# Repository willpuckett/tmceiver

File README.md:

# TMCeiver

A drop in CAN transceiver for Robin Nano V3. 

TMCeiver utilizes a spare stepper slot on Robin Nano V3 to provide CAN connectivity. 

## Features

- CANFD capable (not yet supported in Klipper)
- Excellent reliability—no CAN retransmits in several months of testing
- Jumperable 120 Ω termination resistor
- Less cabling to crimp

## Installation

Start with power off.

1. Remove the stepper driver from the slot you want to use.
2. Make sure the steppers are jumpered to run at 5v. <br />
3. Use jumpers to jump the MISO and SCK pins to the TMCeiver. MISO and SCK are the first and third pins from the mcu side of the stepper slot.  If you're not sure, you can jumper the entire row (all four pins). <br /> or 
4. Insert TMCeiver into the slot, aligning the EN silkscreen with the EN slot on the board (for rev3, align the octule icon with EN). If you get it backwards, nothing will be damaged, but it won't work. <br />
5. Connect the CAN bus to the JST XH connector. 
6. Terminate the CAN bus by placing a jumper on the pins labeled `TERM`.
7. You can connect a second CAN device to the other JST XH connector, in which case you should remove the jumper from the `TERM` pins and terminate the bus at the last device.
8. Compile and flash your board (Use pins 'PD0/PD1' for the CAN bus) with the [Katapult](https://github.com/arksine/katapult) bootloader. You can build the Katapult Deployer and flash it via SD Card, or follow [these instructions](https://github.com/willpuckett/config/blob/main/reference/MKS/Robin_Nano_V3.1.md#flashing-katapult) to flash with OpenOCD.
9. Flash [Klipper](https://github.com/klipper3d/klipper). If you're connecting to the CAN bus with USB via the Robin Nano V3, you'll need to compile in CAN bus bridge mode. 

## Schematic

## Acquisition

Use the files in [production_files](jlcpcb/production_files/) directory to order the PCB from your favorite board house. If you're trying to lower costs, you can opt for assembly on the bottom side only, and hand solder the top side components.

There's also a couple available from my first run [here](https://octule.com).

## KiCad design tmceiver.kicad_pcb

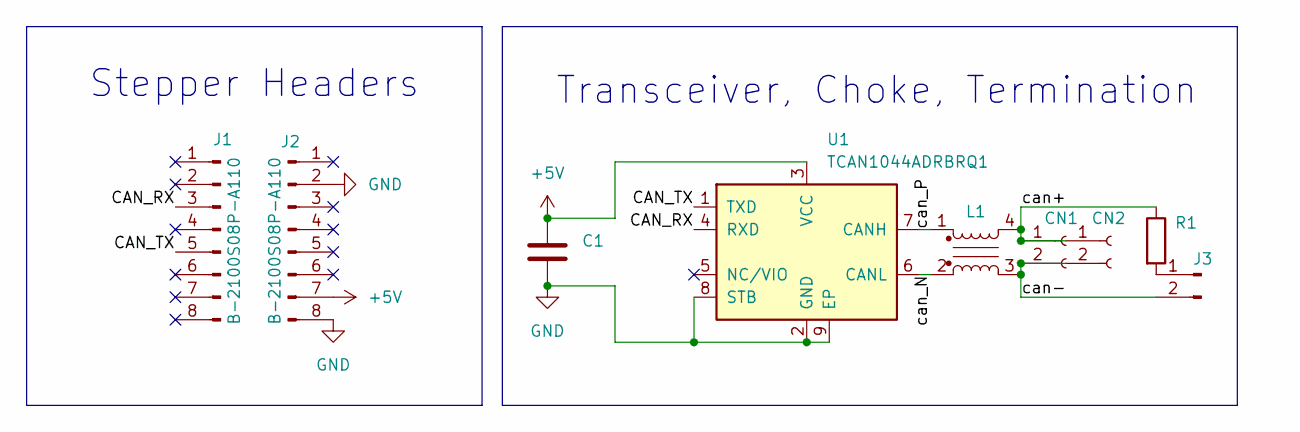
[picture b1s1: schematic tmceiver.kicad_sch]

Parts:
C1: CL10B104KB8NNNC; C_0603_1608Metric
CN1, CN2: B2B-XH-A (LF)(SN); JST_XH_B2B-XH-A_1x02_P2.50mm_Vertical
J1, J2: B-2100S08P-A110; PinHeader_1x08_P2.54mm_Vertical
J3: ZX-PZ2.0-1-2PZZ; PinHeader_1x02_P2.00mm_Vertical
L1: ACT1210-510-2P-TL00; CHOKE_10-2P-TL00_TDK
R1: RC0805FR-07120RL; R_0805_2012Metric
U1: TCAN1044ADRBRQ1; VSON-8-1EP_3x3mm_P0.65mm_EP1.65x2.4mm

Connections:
+5V: C1.1, J2.7, U1.3 (VCC)
/CAN_RX: J1.3, U1.4 (RXD)
/CAN_TX: J1.5, U1.1 (TXD)
/can+: CN1.1, CN2.1, L1.4, R1.1
/can-: CN1.2, CN2.2, J3.2, L1.3
/can_N: L1.2, U1.6 (CANL)
/can_P: L1.1, U1.7 (CANH)
GND: C1.2, J2.2, J2.8, U1.2 (GND), U1.8 (STB), U1.9 (EP)
unnamed: J3.1, R1.2

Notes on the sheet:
Transceiver, Choke, Termination
Stepper Headers

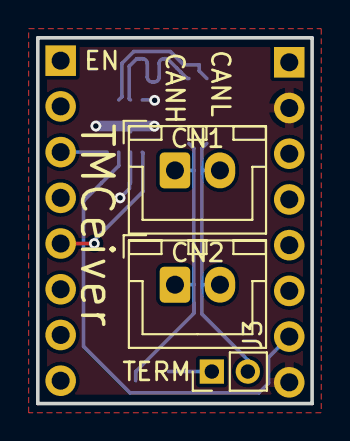
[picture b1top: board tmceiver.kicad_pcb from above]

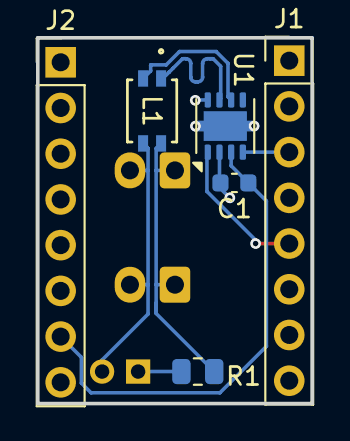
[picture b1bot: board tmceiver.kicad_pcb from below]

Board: 2 copper layers, 15.2 x 20.3 mm, 9 parts (6 on the bottom side), 9 nets.

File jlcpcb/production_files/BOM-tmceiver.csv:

Comment,Designator,Footprint,LCSC
RC0805FR-07120RL,R1,R_0805_2012Metric,C114245
B-2100S08P-A110,"J1,J2",PinHeader_1x08_P2.54mm_Vertical,C124381
B2B-XH-A (LF)(SN),"CN1,CN2",JST_XH_B2B-XH-A_1x02_P2.50mm_Vertical,C158012
CL10B104KB8NNNC,C1,C_0603_1608Metric,C1591
TCAN1044ADRBRQ1,U1,VSON-8-1EP_3x3mm_P0.65mm_EP1.65x2.4mm,C3234118
ZX-PZ2.0-1-2PZZ,J3,PinHeader_1x02_P2.00mm_Vertical,C7501287
ACT1210-510-2P-TL00,L1,CHOKE_10-2P-TL00_TDK,C95572

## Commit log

2025-04-17 add images to install instructions
